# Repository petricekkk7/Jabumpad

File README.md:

# Jabumpad
a hackpad from me
i  used AI just for the firmvare took me like 8hours min  
hardest thing was the PCB 
the tutorial is pretty confusing for me so if i got somting wrong am sorry

SCHEMATIC

THE PCB LAYOUT

A VIEW OF THE PCB IM 3D VIEWER

THE CASE 

    IF I MISSED SOMTING AM SORRY

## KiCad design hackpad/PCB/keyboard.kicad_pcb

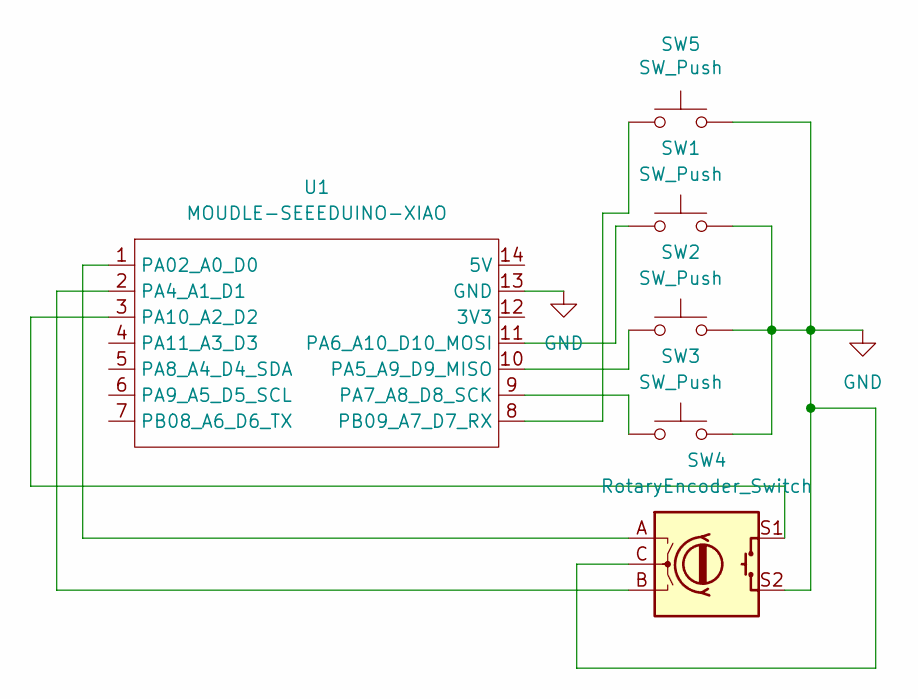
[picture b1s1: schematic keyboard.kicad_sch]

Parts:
SW1, SW2, SW3, SW5: SW_Push; SW_Cherry_MX_1.00u_PCB
SW4: RotaryEncoder_Switch; RotaryEncoder_Alps_EC11E-Switch_Vertical_H20mm
U1: MOUDLE-SEEEDUINO-XIAO; XIAO-Generic-Hybrid-14P-2.54-21X17.8MM

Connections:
GND: SW1.2, SW2.2, SW3.2, SW4.C, SW4.S2, SW5.2, U1.13 (GND)
unnamed: SW4.A, U1.1 (PA02_A0_D0)
unnamed: SW4.B, U1.2 (PA4_A1_D1)
unnamed: SW2.1, U1.10 (PA5_A9_D9_MISO)
unnamed: SW1.1, U1.11 (PA6_A10_D10_MOSI)
unnamed: SW3.1, U1.9 (PA7_A8_D8_SCK)
unnamed: SW4.S1, U1.3 (PA10_A2_D2)
unnamed: SW5.1, U1.8 (PB09_A7_D7_RX)

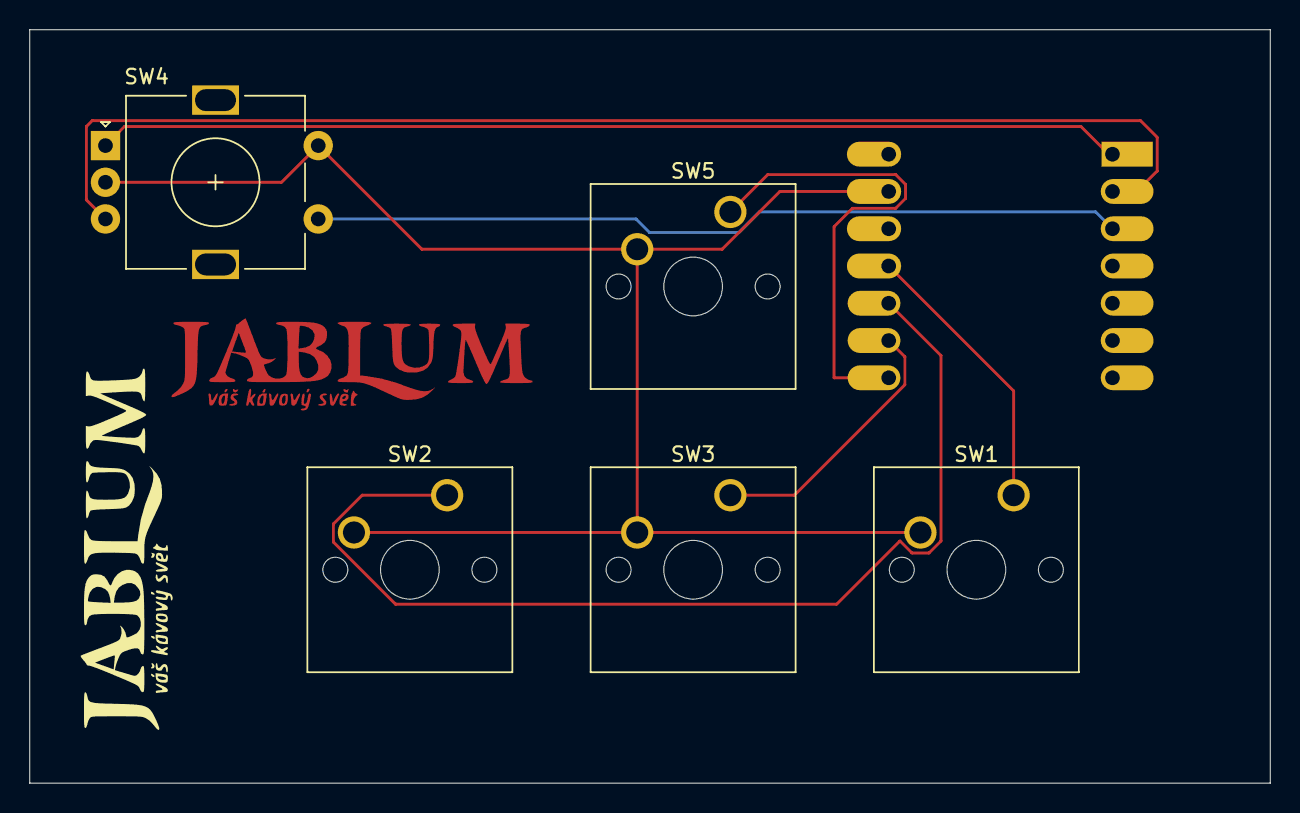
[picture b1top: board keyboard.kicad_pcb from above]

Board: 2 copper layers, 84.5 x 51.3 mm, 6 parts (1 on the bottom side), 8 nets.

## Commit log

2026-06-17 Enhance README with PCB and firmware details
    Added detailed information about the PCB, case, and firmware setup for the Jabumpad project, including images and code snippets.
2026-06-17 Remove keyboard firmware setup from README
    Removed firmware initialization and configuration code for the keyboard.
2026-06-17 Fix typos in README.md
    Corrected spelling and grammar in the README.
2026-06-17 Fix typo in README.md
